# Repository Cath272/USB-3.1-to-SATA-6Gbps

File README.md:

# USB-3.1-to-SATA-6Gbps
USB 3.2 gen 2 (SuperSpeed+ 10Gbps) to SATA 6Gbps

This Board is based on the VIA Labs VL716 

## VL716

- High performance, low power single chip USB 3.1 to SATA 6Gb/s bridge controller 
- USB Type-C connector support
###  Built-in Voltage Regulators

- 5.0V to 3.3V LDO

- 5.0V to 1.2V switching DC-DC

## Other Parts 

- USB C 24P Connector (THT inside pins)
- 25Mhz Crystal for Ic
- Sata 22P horizontal female SMD connector
- W25Q16BVSSIG 16Mbit SPI Flash  Memory
- 1.5uH/2.2uH Inductor
- Power/Busy LEDs

## PCB 
This board uses a 4 layer stackup with a  1.6mm thickness:

- POWER/SIGNAL

- GND
  
- GND
  
- POWER/SIGNAL

High Speed diferential lines need a refrence ground plane so internal planes are ground referance planes for the High speed USB lines

The Pcb was inspired by similar boards that use VL711/VL715 Ics. The capacitors are standard values that are use as decoupling capacitors.

### Schematic:

## PCB Screenshots

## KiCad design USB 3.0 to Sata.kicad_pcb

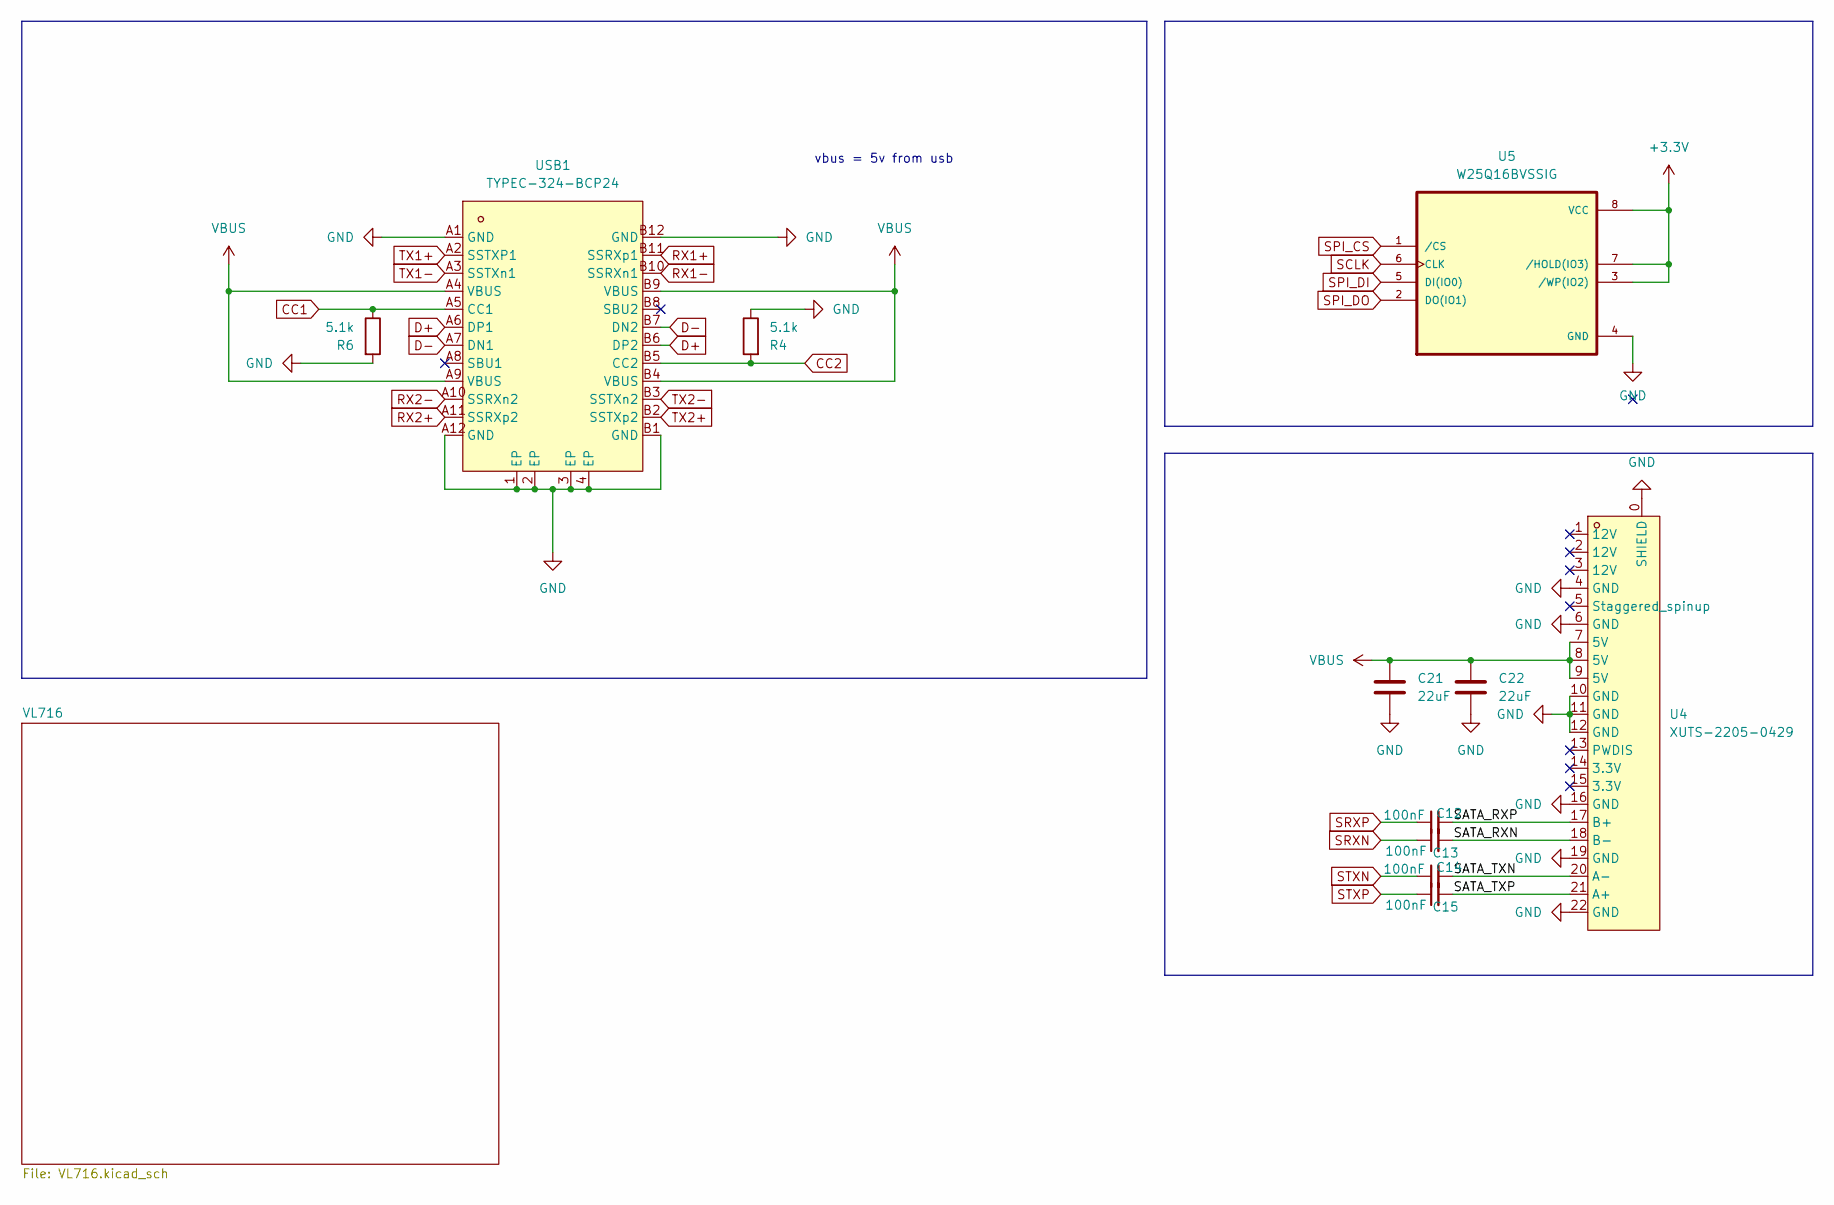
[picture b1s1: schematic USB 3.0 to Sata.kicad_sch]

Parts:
C12, C13, C14, C15: 100nF; C_0402_1005Metric
C21, C22: 22uF; C_0805_2012Metric
R4, R6: 5.1k; R_0402_1005Metric
U4: XUTS-2205-0429; CONN-SMD_UTS-2205-0429; LCSC Part C7527511
U5: W25Q16BVSSIG; SOIC-8_L5.3-W5.3-P1.27-LS8.0-BL; PARTREV F
USB1: TYPEC-324-BCP24; USB-C-SMD_TYPEC-324-BCP24; LCSC Part C2835314

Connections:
+3.3V: U5.3 (/WP(IO2)), U5.7 (/HOLD(IO3)), U5.8 (VCC); also elsewhere on the board
/SATA_RXN: C13.2, U4.18 (B-)
/SATA_RXP: C12.2, U4.17 (B+)
/SATA_TXN: C14.2, U4.20 (A-)
/SATA_TXP: C15.2, U4.21 (A+)
CC1: R6.1, USB1.A5 (CC1); also elsewhere on the board
CC2: R4.2, USB1.B5 (CC2); also elsewhere on the board
D+: USB1.A6 (DP1), USB1.B6 (DP2); also elsewhere on the board
D-: USB1.A7 (DN1), USB1.B7 (DN2); also elsewhere on the board
GND: C21.2, C22.2, R4.1, R6.2, U4.0 (SHIELD), U4.4 (GND), U4.6 (GND), U4.10 (GND), U4.11 (GND), U4.12 (GND), U4.16 (GND), U4.19 (GND), U4.22 (GND), U5.4 (GND), USB1.1 (EP), USB1.2 (EP), USB1.3 (EP), USB1.4 (EP), USB1.A1 (GND), USB1.A12 (GND), USB1.B1 (GND), USB1.B12 (GND); also elsewhere on the board
RX1+: USB1.B11 (SSRXp1); also elsewhere on the board
RX1-: USB1.B10 (SSRXn1); also elsewhere on the board
RX2+: USB1.A11 (SSRXp2); also elsewhere on the board
RX2-: USB1.A10 (SSRXn2); also elsewhere on the board
SCLK: U5.6 (CLK); also elsewhere on the board
SPI_CS: U5.1 (/CS); also elsewhere on the board
SPI_DI: U5.5 (DI(IO0)); also elsewhere on the board
SPI_DO: U5.2 (DO(IO1)); also elsewhere on the board
SRXN: C13.1; also elsewhere on the board
SRXP: C12.1; also elsewhere on the board
STXN: C14.1; also elsewhere on the board
STXP: C15.1; also elsewhere on the board
TX1+: USB1.A2 (SSTXP1); also elsewhere on the board
TX1-: USB1.A3 (SSTXn1); also elsewhere on the board
TX2+: USB1.B2 (SSTXp2); also elsewhere on the board
TX2-: USB1.B3 (SSTXn2); also elsewhere on the board
VBUS: C21.1, C22.1, U4.7 (5V), U4.8 (5V), U4.9 (5V), USB1.A4 (VBUS), USB1.A9 (VBUS), USB1.B4 (VBUS), USB1.B9 (VBUS); also elsewhere on the board

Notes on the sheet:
vbus = 5v from usb

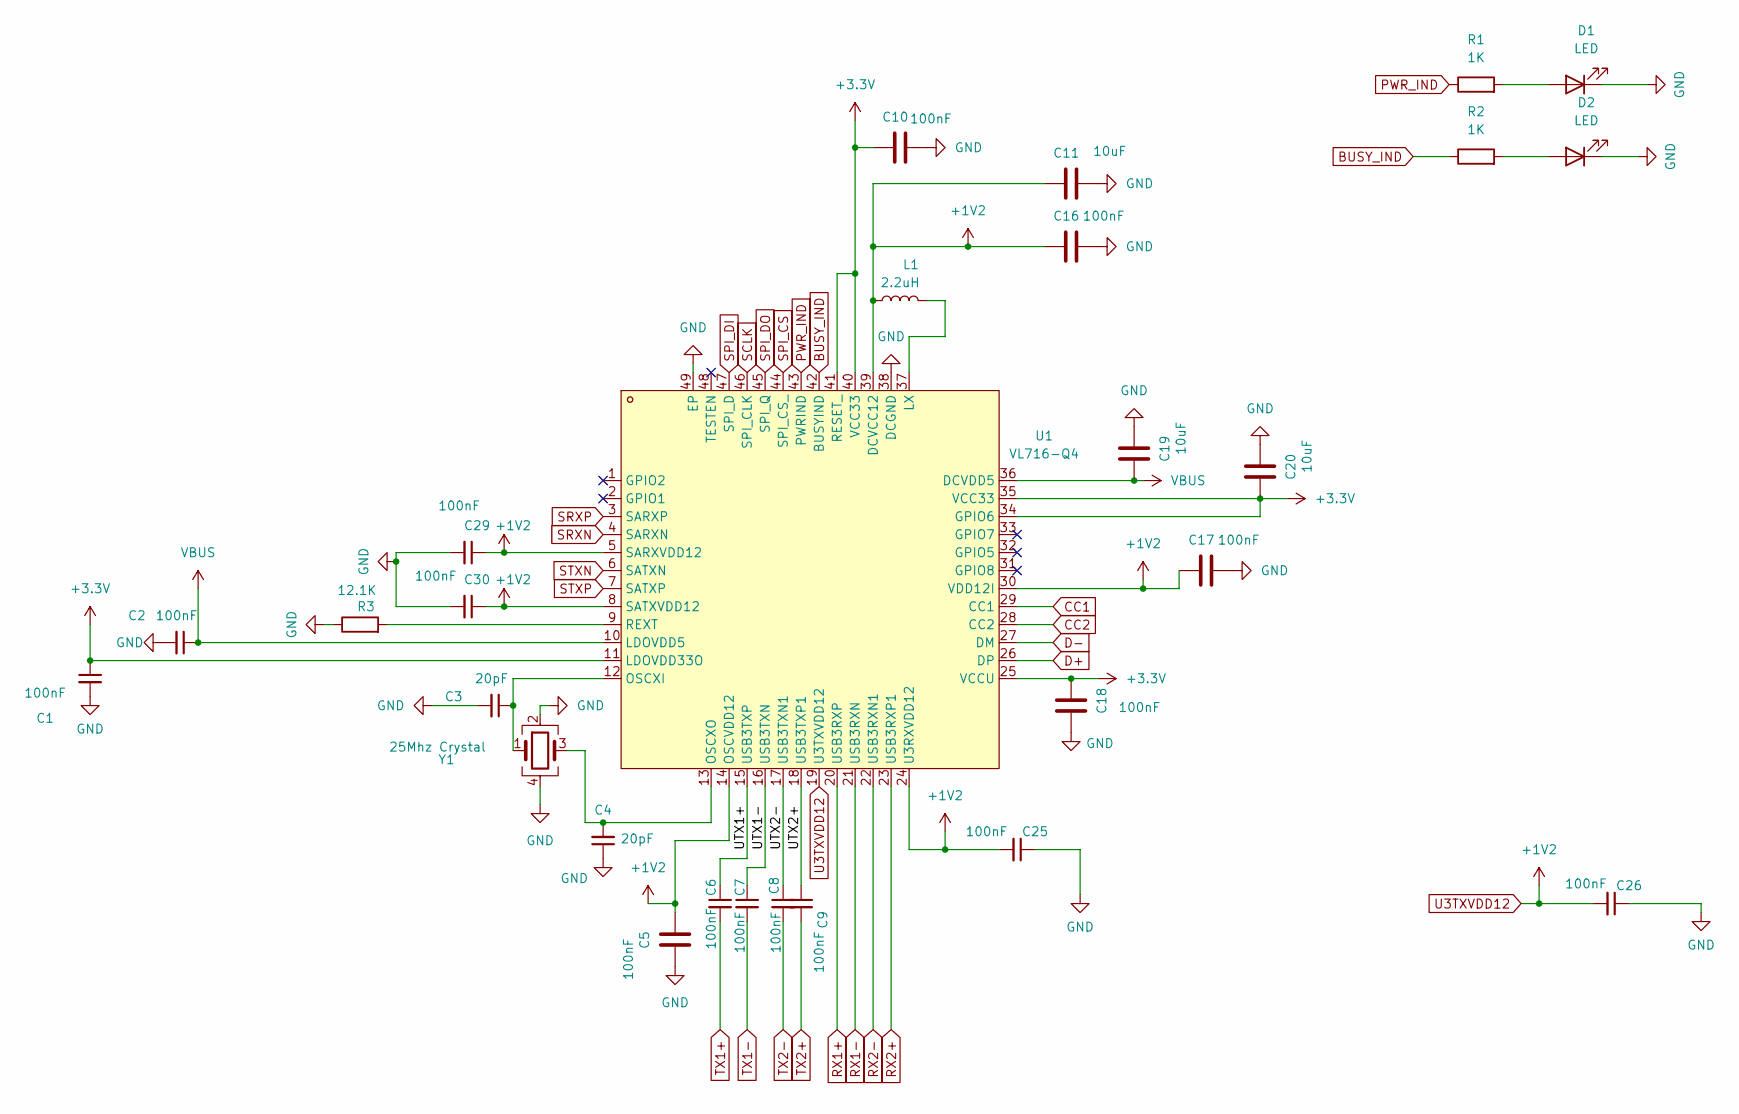
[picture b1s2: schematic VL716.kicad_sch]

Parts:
C1, C2, C5, C6, C7, C8, C9, C10, C16, C17, C18, C25, C26, C29, C30: 100nF; C_0402_1005Metric
C3, C4: 20pF; C_0402_1005Metric
C11, C19, C20: 10uF; C_0805_2012Metric
D1, D2: LED; LED_0603_1608Metric
L1: 2.2uH; L_Cenker_CKCS4030
R1, R2: 1K; R_0402_1005Metric
R3: 12.1K; R_0402_1005Metric
U1: VL716-Q4; QFN-48_L6.0-W6.0-P0.40-BL-EP3.8; LCSC Part C69727
Y1: 25Mhz Crystal; Crystal_SMD_3225-4Pin_3.2x2.5mm

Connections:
+3.3V: C1.1, C10.1, C18.1, C20.2, U1.11 (LDOVDD33O), U1.25 (VCCU), U1.34 (GPIO6), U1.35 (VCC33), U1.40 (VCC33), U1.41 (RESET_); also elsewhere on the board
/VL716/UTX1+: C6.1, U1.15 (USB3TXP)
/VL716/UTX1-: C7.1, U1.16 (USB3TXN)
/VL716/UTX2+: C9.1, U1.18 (USB3TXP1)
/VL716/UTX2-: C8.1, U1.17 (USB3TXN1)
BUSY_IND: R2.1, U1.42 (BUSYIND)
CC1: U1.29 (CC1); also elsewhere on the board
CC2: U1.28 (CC2); also elsewhere on the board
D+: U1.26 (DP); also elsewhere on the board
D-: U1.27 (DM); also elsewhere on the board
GND: C1.2, C2.2, C3.2, C4.1, C5.1, C10.2, C11.2, C16.2, C17.2, C18.2, C19.1, C20.1, C25.1, C26.1, C29.2, C30.2, D1.1 (K), D2.1 (K), R3.1, U1.38 (DCGND), U1.49 (EP), Y1.2, Y1.4; also elsewhere on the board
unnamed: D1.2 (A), R1.2
unnamed: D2.2 (A), R2.2
unnamed: L1.2, U1.37 (LX)
unnamed: C3.1, U1.12 (OSCXI), Y1.1
unnamed: C4.2, U1.13 (OSCXO), Y1.3
unnamed: R3.2, U1.9 (REXT)
PWR_IND: R1.1, U1.43 (PWRIND)
RX1+: U1.20 (USB3RXP); also elsewhere on the board
RX1-: U1.21 (USB3RXN); also elsewhere on the board
RX2+: U1.23 (USB3RXP1); also elsewhere on the board
RX2-: U1.22 (USB3RXN1); also elsewhere on the board
SCLK: U1.46 (SPI_CLK); also elsewhere on the board
SPI_CS: U1.44 (SPI_CS_); also elsewhere on the board
SPI_DI: U1.47 (SPI_D); also elsewhere on the board
SPI_DO: U1.45 (SPI_Q); also elsewhere on the board
SRXN: U1.4 (SARXN); also elsewhere on the board
SRXP: U1.3 (SARXP); also elsewhere on the board
STXN: U1.6 (SATXN); also elsewhere on the board
STXP: U1.7 (SATXP); also elsewhere on the board
TX1+: C6.2; also elsewhere on the board
TX1-: C7.2; also elsewhere on the board
TX2+: C9.2; also elsewhere on the board
TX2-: C8.2; also elsewhere on the board
U3TXVDD12: C5.2, C11.1, C16.1, C17.1, C25.2, C26.2, C29.1, C30.1, L1.1, U1.5 (SARXVDD12), U1.8 (SATXVDD12), U1.14 (OSCVDD12), U1.19 (U3TXVDD12), U1.24 (U3RXVDD12), U1.30 (VDD12I), U1.39 (DCVCC12)
VBUS: C2.1, C19.2, U1.10 (LDOVDD5), U1.36 (DCVDD5); also elsewhere on the board

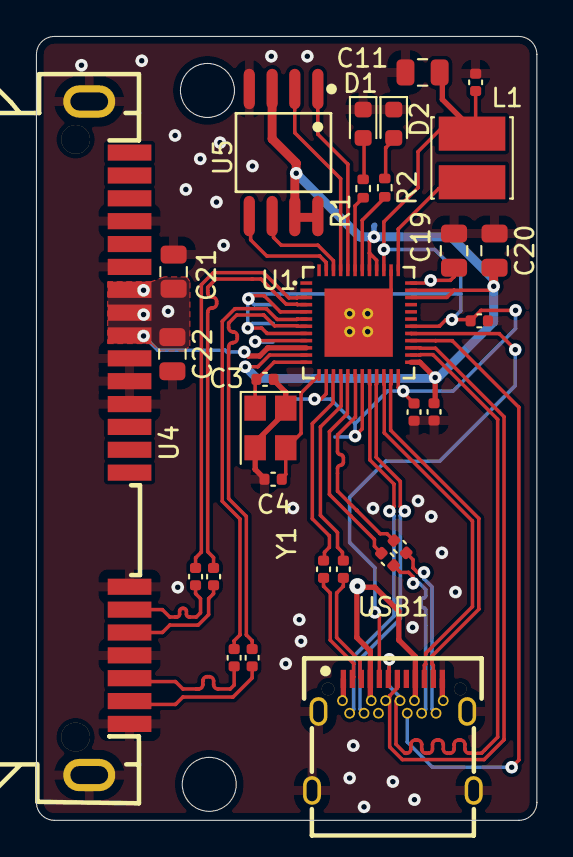
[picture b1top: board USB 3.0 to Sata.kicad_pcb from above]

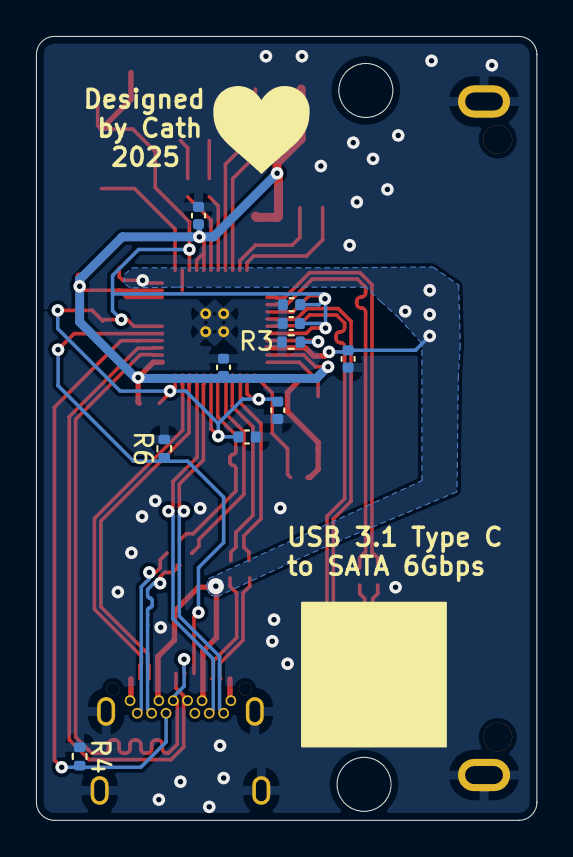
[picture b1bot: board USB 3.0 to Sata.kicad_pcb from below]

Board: 4 copper layers, 27.8 x 43.5 mm, 39 parts (10 on the bottom side), 40 nets.

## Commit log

2025-02-05 Updated Schematic and Uploaded PCB files
2025-02-05 Updated PCB Pictures
2025-02-21 Fixed pcb errors
    Fixed RX2 TX2 lines being flipped, changed usb port footprint to the corect one, changed flash footprint from SOP8-150MIL to SOP8-208MIL
2025-03-05 Fixed layout
    Fixed traces length
